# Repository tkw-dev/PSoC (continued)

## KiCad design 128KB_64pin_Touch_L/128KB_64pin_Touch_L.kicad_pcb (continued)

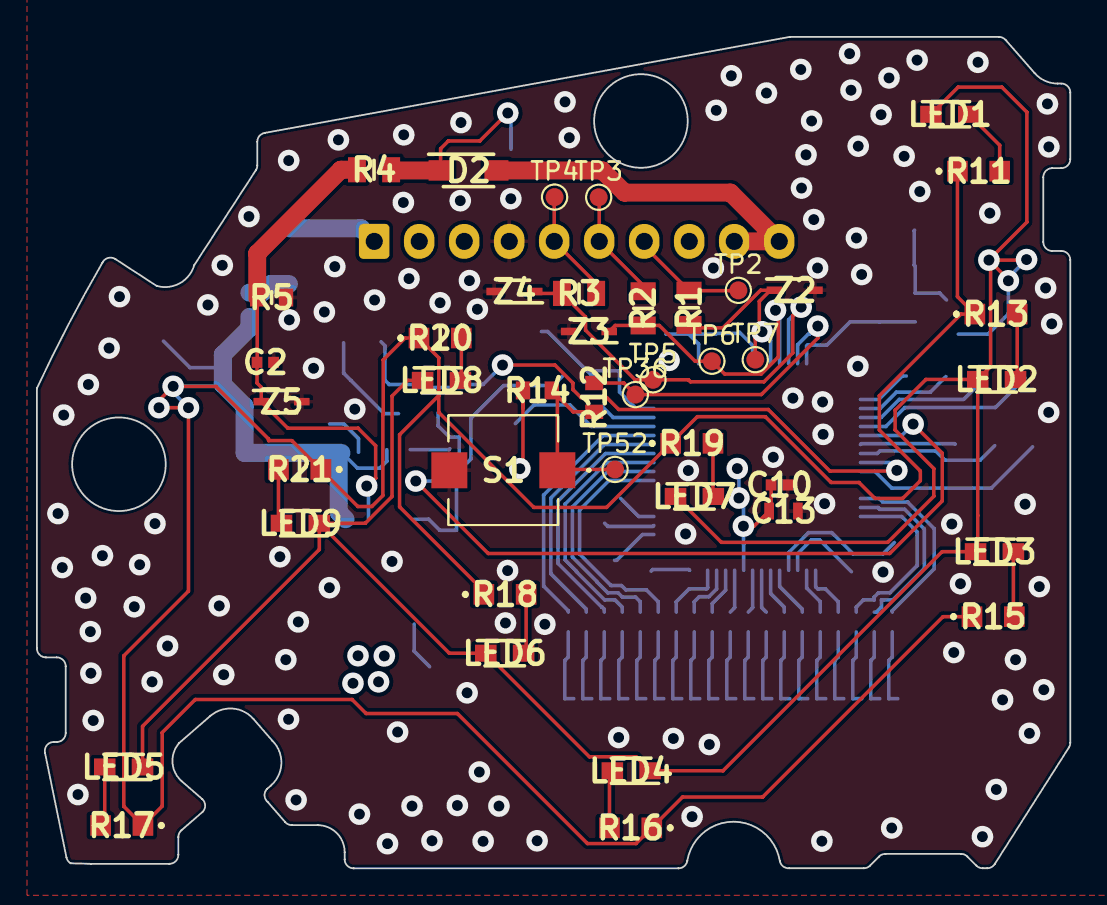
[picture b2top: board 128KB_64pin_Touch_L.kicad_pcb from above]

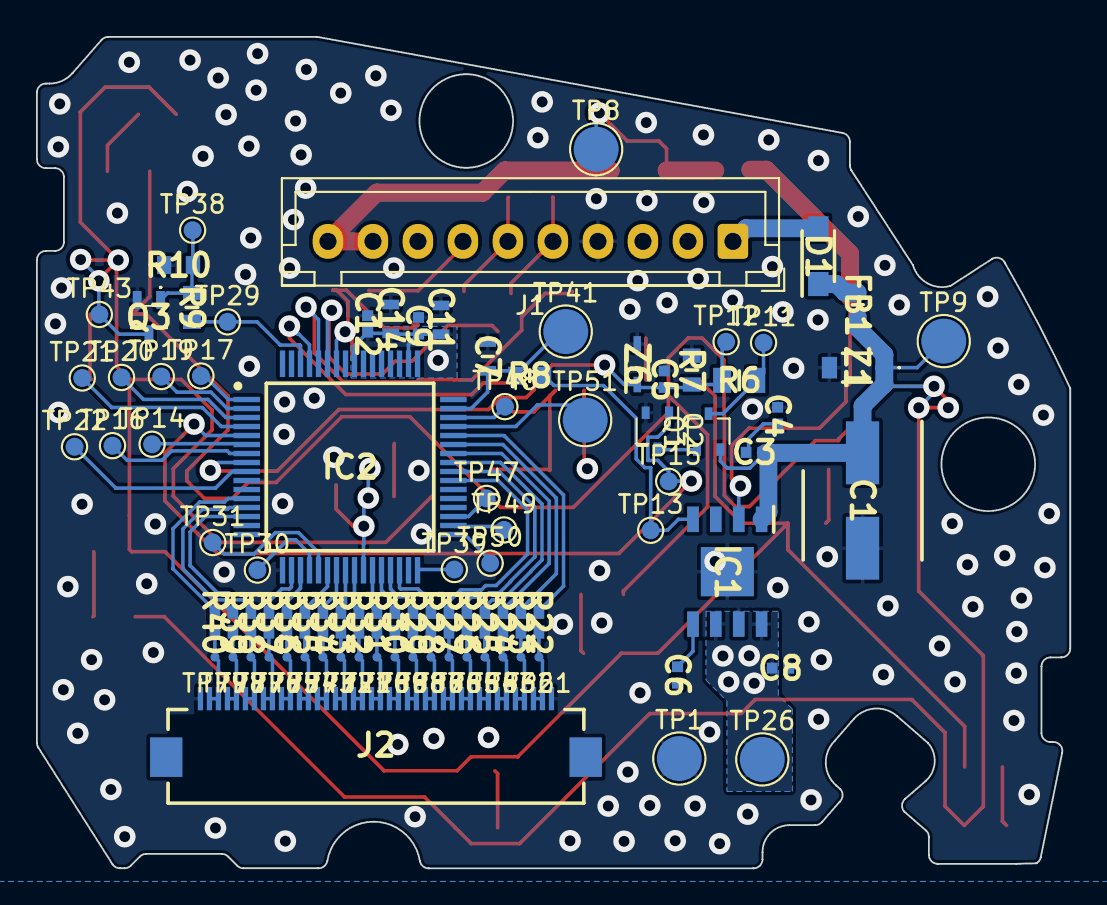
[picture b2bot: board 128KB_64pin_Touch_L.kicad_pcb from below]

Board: 4 copper layers, 57.4 x 46.2 mm, 134 parts (92 on the bottom side), 89 nets.

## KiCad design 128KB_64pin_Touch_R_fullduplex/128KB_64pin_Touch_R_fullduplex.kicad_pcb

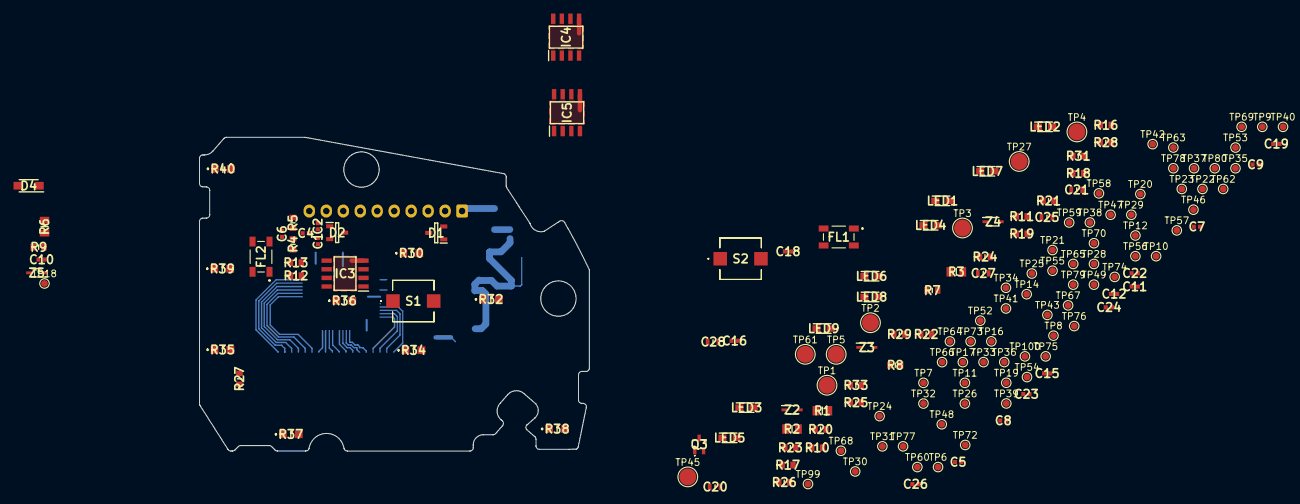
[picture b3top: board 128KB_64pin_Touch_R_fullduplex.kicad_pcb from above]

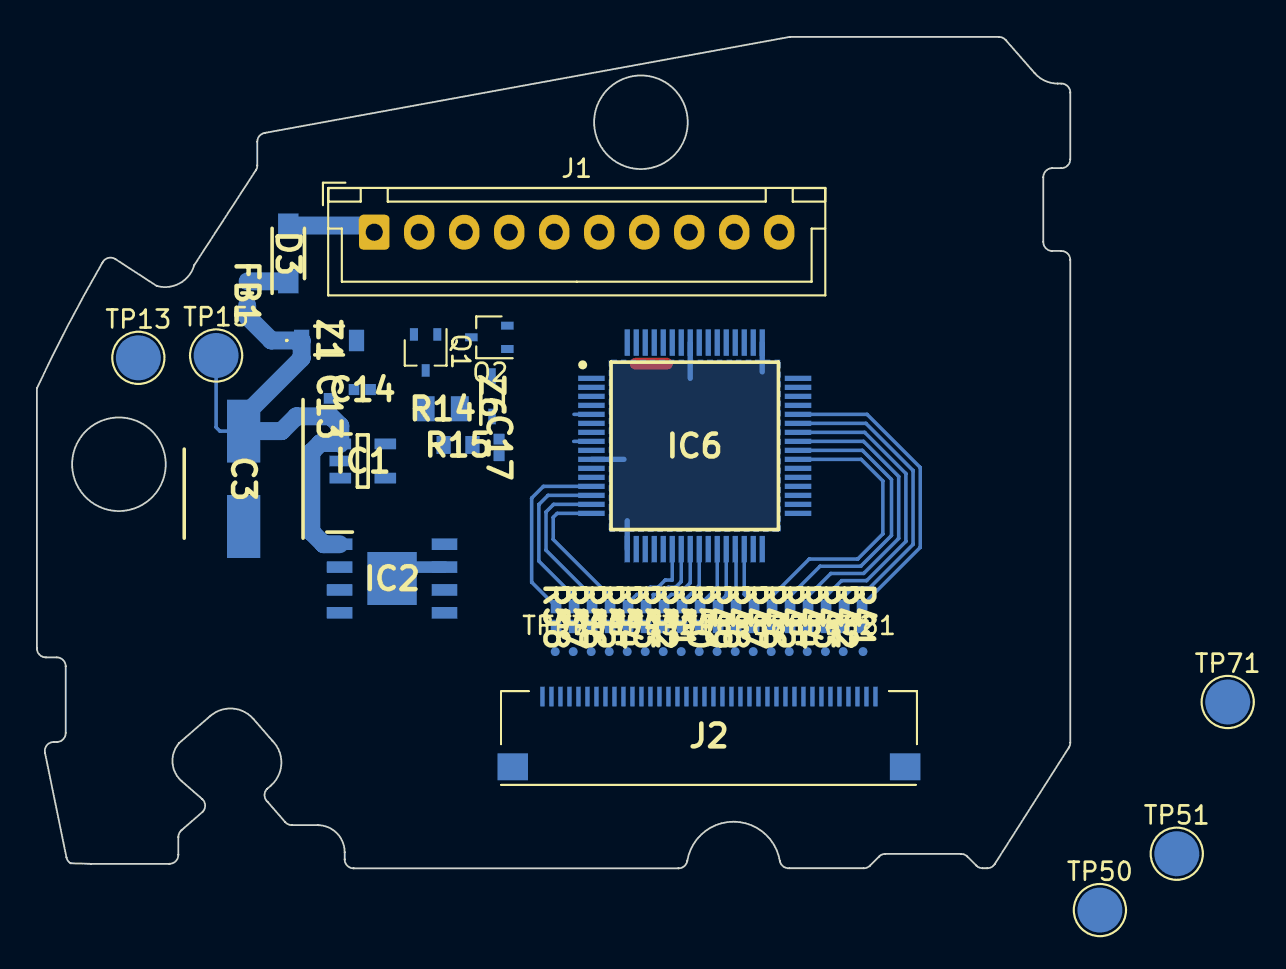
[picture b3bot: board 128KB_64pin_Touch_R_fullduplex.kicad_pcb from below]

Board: 4 copper layers, 57.4 x 46.2 mm, 220 parts (58 on the bottom side), 123 nets.

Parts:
C1, C2, C4, C5, C6, C7, C8, C9, C11, C12, C13, C14, C15, C16, C18, C22, C23, C24, C26: GCM155R71H104KE02D; CAPC1005X55N
C3: UCQ1V470MCL1GS; CAPAE660X780N
C10, C17: GRM155R71C104KA88D; CAPC1005X55N
C19: GCM155L81E103KA37D; CAPC1005X55N
C20: CL10B104JB8NNNC; CAPC1608X90N
C21, C25, C27, C28: CGA3E2X5R1A105M080AA; CAPC1608X90N
D1, D2: PESD5V0L2BT,215; SOT95P230X110-3N
D3, D4: M1F60-6063; SODFL3918X140N
FB1: BLM18KG601SZ1D; BLM18EG121SH1D
FL1, FL2: DLW43SH510XK2L; DLW43SH110XK2K
IC1: S-19212D50A-M5T1U; SOT95P275X130-5N
IC2: R5112S121B-E2-KE; SOIC127P620X160-9N
IC3: SN65LBC179AD; SOIC127P600X175-8N
IC4, IC5: SN65LBC176QDRG4Q1; SOIC127P600X175-8N
IC6: CY8C4146AZI-S455; QFP50P1200X1200X160-64N
J1: Conn_01x10; JST_XH_B10B-XH-A_1x10_P2.50mm_Vertical
J2: XF2M-3815-1A-R100; XF2M38151AR100
LED1, LED2, LED3, LED4, LED5, LED6, LED7, LED8, LED9: VLMR233T2V2-GS08; LEDM2214X140N
Q1: BC807W; SOT-323_SC-70
Q2: BC848W; SOT-323_SC-70
Q3: SSM3K7002KFU,LF; SSM3K7002CFULF
R1, R2, R3, R6, R14: RMC1/10K683FTP83; RESC2012X65N
R4, R5, R7, R8: RMC1/16SK60R4FTH; RESC1608X55N
R9, R15, R28, R29, R31, R33: RMC1/16SK103FTH43; RESC1608X55N
R10, R11, R12, R13, R16, R17, R18, R19, R21, R22, R23, R24, R25, R26, R27: RMC16K270FTP; RESC1608X55N
R20: RMC16K102FTP; RESC1608X55N
R30, R32, R34, R35, R36, R37, R38, R39, R40: ERJ-6ENF1502V; ERJ6ENF1000V
R41, R42, R43, R44, R45, R46, R47, R48, R49, R50, R51, R52, R53, R54, R55, R56, R57, R58: ERJ-2GEJ561X; RESC1005X40N
S1, S2: SKTRAEE010
TP1, TP2, TP3, TP4, TP5, TP13, TP15, TP27, TP45, TP50, TP51, TP61, TP71: TestPoint; TestPoint_Pad_D2.5mm
TP6, TP7, TP8, TP9, TP10, TP11, TP12, TP14, TP16, TP17, TP18, TP19, TP20, TP21, TP22, TP23, TP24, TP25, TP26, TP28, TP29, TP30, TP31, TP32, TP33, TP34, TP35, TP36, TP37, TP38, TP39, TP40, TP41, TP42, TP43, TP46, TP47, TP48, TP49, TP52, TP53, TP54, TP55, TP56, TP57, TP58, TP59, TP60, TP62, TP63, TP64, TP65, TP66, TP67, TP68, TP69, TP70, TP72, TP73, TP74, TP75, TP76, TP77, TP78, TP79, TP80, TP99, TP100: TestPoint; TestPoint_Pad_D1.0mm
TP81, TP82, TP83, TP84, TP85, TP86, TP87, TP88, TP89, TP90, TP91, TP92, TP93, TP94, TP95, TP96, TP97, TP98: TestPoint; TestPoint_Pad_D0.5mm
Z1: KDZVTR36B
Z2, Z3, Z4, Z5, Z6: UDZVFHTE5.6B; SODFL2512X90N

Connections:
+5V: C22.1, C23.1, C24.1, C25.1, C26.1, C27.1, C28.1, IC2.6 (SENSE), IC2.8 (VOUT), IC6.26 (VDDD_1), IC6.50 (VDDD_2), IC6.56 (VDDA), R16.2, R21.2, R33.2, TP45.1
+5VD: C21.1, IC1.5 (VOUT), R17.2, R25.2, TP27.1
+BATT: C3.1, C8.1, C13.1, FB1.2, IC1.1 (VIN), IC2.1 (VDD), LED1.2, LED2.2, LED3.2, LED4.2, LED5.2, LED6.2, LED7.2, LED8.2, LED9.2, Q1.2 (E), TP15.1, Z1.1
GND: C1.2, C2.1, C3.2, C4.2, C7.2, C9.2, C10.2, C11.2, C12.1, C14.2, C15.2, C16.2, C17.2, C18.2, C19.2, C20.1, C21.2, C22.2, C23.2, C24.2, C25.2, C26.2, C27.2, C28.2, D1.3 (DOUBLE_CATHODE), D2.3 (DOUBLE_CATHODE), IC1.2 (VSS), IC2.7 (GND), IC2.9 (EP), IC3.4 (GND), IC4.5 (GND), IC5.5 (GND), IC6.10 (VSSD_1), IC6.17 (VSSD_2), IC6.49 (VSSD_3), IC6.57 (VSSA), J1.4, J2.1, J2.38, Q2.2 (E), Q3.2, R9.1, R15.1, R22.2, R23.2, R24.2, R29.2, S1.2, S2.2, TP5.1, Z1.2, Z2.2, Z3.2, Z4.2, Z5.2, Z6.2
unnamed: C1.1, C6.1, D2.2 (CATHODE_2), FL2.1, FL2.2, J1.8, R4.1, R12.1, TP3.1
unnamed: C2.2, C6.2, D2.1 (CATHODE_1), FL2.3, FL2.4, J1.9, R5.2, R13.1, TP4.1
unnamed: C4.1, R4.2, R5.1, TP12.1
unnamed: C7.1, R7.2, R8.1, TP14.1
unnamed: C8.2, C9.1
unnamed: C10.1, IC2.2 (CE), R6.2, R9.2, TP18.1, Z5.1
unnamed: C5.1, C11.1, D1.2 (CATHODE_2), FL1.1, FL1.2, J1.2, R7.1, R10.1, TP1.1
unnamed: C5.2, C12.2, D1.1 (CATHODE_1), FL1.3, FL1.4, J1.3, R8.2, R11.1, TP2.1
unnamed: C13.2, C14.1, TP16.1
unnamed: C15.1, C16.1, C18.1, IC3.1 (VCC), IC4.8 (VCC), IC5.8 (VCC), R16.1, R17.1
unnamed: C17.1, IC6.8 (P2.6), R14.2, R15.2, TP23.1, Z6.1
unnamed: C19.1, IC2.5 (CD)
unnamed: C20.2, IC6.47 (XRES), R20.1, TP38.1, TP61.1
unnamed: D3.1, FB1.1
unnamed: D3.2, J1.1
unnamed: D4.1, R6.1, TP13.1
unnamed: D4.2, J1.10
unnamed: IC1.4 (ON/OFF), IC5.3 (DE), IC6.5 (P2.3), Q2.1 (B), R24.1, TP31.1, TP33.1
unnamed: IC2.4 (DOUT), R20.2, TP24.1
unnamed: IC3.2 (R), R18.1, TP26.1
unnamed: IC3.3 (D), R19.1, TP25.1
unnamed: IC3.5 (Y), IC5.6 (A), R13.2, TP20.1
unnamed: IC3.6 (Z), IC5.7 (B), R12.2, TP19.1
unnamed: IC3.7 (B), IC4.7 (B), R11.2, TP22.1
unnamed: IC3.8 (A), IC4.6 (A), R10.2, TP21.1
unnamed: IC4.1 (R), R26.2
unnamed: IC4.2 (~RE), IC6.1 (P1.7), R21.1, R25.1, TP36.1
unnamed: IC4.3 (DE), R23.1, TP37.1
unnamed: IC4.4 (D), TP30.1
unnamed: IC5.1 (R), TP28.1
unnamed: IC5.2 (~RE), R22.1, TP29.1
unnamed: IC5.4 (D), R27.2, TP35.1
unnamed: IC6.2 (P2.0), TP40.1
unnamed: IC6.3 (P2.1), TP41.1
unnamed: IC6.4 (P2.2), TP42.1
unnamed: IC6.6 (P2.4), R18.2, R26.1, TP32.1
unnamed: IC6.7 (P2.5), R19.2, TP34.1
unnamed: IC6.9 (P2.7), TP43.1
unnamed: IC6.13 (P6.1), R58.1
unnamed: IC6.14 (P6.2), R57.1
unnamed: IC6.15 (P6.4), R56.1
unnamed: IC6.16 (P6.5), R55.1
unnamed: IC6.18 (P3.0), TP46.1
unnamed: IC6.19 (P3.1), R27.1, TP39.1
unnamed: IC6.20 (P3.2), TP50.1
unnamed: IC6.21 (P3.3), TP51.1
unnamed: IC6.22 (P3.4), R54.1
unnamed: IC6.23 (P3.5), R53.1
unnamed: IC6.24 (P3.6), R52.1
unnamed: IC6.25 (P3.7), R51.1
unnamed: IC6.27 (P4.0), R50.1
unnamed: IC6.28 (P4.1), R49.1
unnamed: IC6.29 (P4.2), R48.1
unnamed: IC6.30 (P4.3), R47.1
unnamed: IC6.31 (P4.4), TP66.1
unnamed: IC6.32 (P4.5), TP59.1
unnamed: IC6.33 (P4.6), TP70.1
unnamed: IC6.34 (P4.7), TP69.1
unnamed: IC6.35 (P5.6), TP67.1
unnamed: IC6.36 (P5.7), TP65.1
unnamed: IC6.37 (P7.0), TP64.1
unnamed: IC6.38 (P7.1), TP60.1
unnamed: IC6.39 (P0.0), R46.1
unnamed: IC6.40 (P0.1), R45.1
unnamed: IC6.41 (P0.2), R44.1
unnamed: IC6.42 (P0.3), R43.1
unnamed: IC6.43 (P0.4), R42.1
unnamed: IC6.44 (P0.5), R41.1
unnamed: IC6.45 (P0.6), TP71.1
unnamed: IC6.46 (P0.7), TP68.1
unnamed: IC6.51 (P5.0), TP57.1
unnamed: IC6.52 (P5.1), TP55.1
unnamed: IC6.53 (P5.2), TP54.1
unnamed: IC6.54 (P5.3), TP53.1
unnamed: IC6.55 (P5.5), TP52.1
unnamed: IC6.58 (P1.0), R1.2, TP11.1, Z2.1
unnamed: IC6.59 (P1.1), R2.2, TP10.1, Z3.1
unnamed: IC6.60 (P1.2), R3.2, TP9.1, Z4.1
unnamed: IC6.61 (P1.3), R31.2, TP56.1
unnamed: IC6.62 (P1.4), R28.2, TP49.1
unnamed: IC6.63 (P1.5), TP48.1
unnamed: IC6.64 (P1.6), TP47.1
unnamed: J1.5, R1.1, TP6.1
unnamed: J1.6, R2.1, TP7.1
unnamed: J1.7, R3.1, TP8.1
unnamed: J2.2, J2.3, R58.2, TP97.1
unnamed: J2.4, J2.5, R57.2, TP98.1
unnamed: J2.6, J2.7, R56.2, TP96.1
unnamed: J2.8, J2.9, R55.2, TP95.1
unnamed: J2.10, J2.11, R54.2, TP94.1
unnamed: J2.12, J2.13, R53.2, TP93.1
unnamed: J2.14, J2.15, R52.2, TP92.1
unnamed: J2.16, J2.17, R51.2, TP91.1
unnamed: J2.18, J2.19, R50.2, TP90.1
unnamed: J2.20, J2.21, R49.2, TP89.1
unnamed: J2.22, J2.23, R48.2, TP88.1
unnamed: J2.24, J2.25, R47.2, TP87.1
unnamed: J2.26, J2.27, R46.2, TP86.1
unnamed: J2.28, J2.29, R45.2, TP85.1
unnamed: J2.30, J2.31, R44.2, TP84.1
unnamed: J2.32, J2.33, R43.2, TP83.1
unnamed: J2.34, J2.35, R42.2, TP82.1
unnamed: J2.36, J2.37, R41.2, TP81.1
unnamed: J2.MP1, TP100.1
unnamed: J2.MP2, TP99.1
unnamed: LED1.1, R30.1, TP62.1
unnamed: LED2.1, R32.1, TP73.1
unnamed: LED3.1, R34.1, TP74.1
unnamed: LED4.1, R35.1, TP75.1
unnamed: LED5.1, R36.1, TP76.1
unnamed: LED6.1, R37.1, TP77.1
unnamed: LED7.1, R38.1, TP78.1
unnamed: LED8.1, R39.1, TP79.1
unnamed: LED9.1, R40.1, TP80.1
unnamed: Q1.1 (B), Q2.3 (C)
unnamed: Q1.3 (C), R14.1, TP17.1
unnamed: Q3.1, R28.1, R29.1, TP58.1
unnamed: Q3.3, R30.2, R32.2, R34.2, R35.2, R36.2, R37.2, R38.2, R39.2, R40.2, TP63.1
unnamed: R31.1, R33.1, S1.1, S2.1, TP72.1

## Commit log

2023-05-07 hoge
